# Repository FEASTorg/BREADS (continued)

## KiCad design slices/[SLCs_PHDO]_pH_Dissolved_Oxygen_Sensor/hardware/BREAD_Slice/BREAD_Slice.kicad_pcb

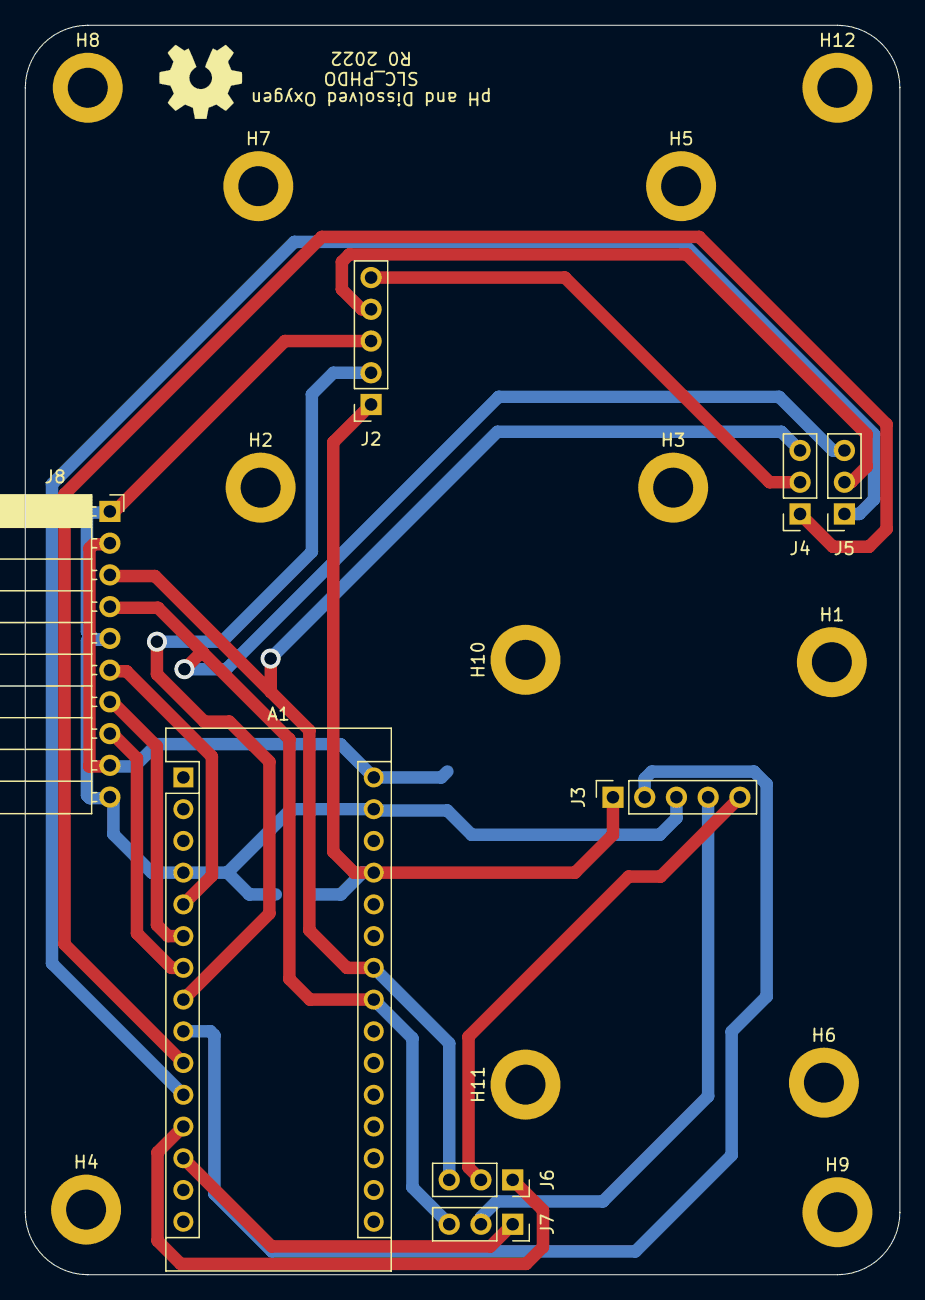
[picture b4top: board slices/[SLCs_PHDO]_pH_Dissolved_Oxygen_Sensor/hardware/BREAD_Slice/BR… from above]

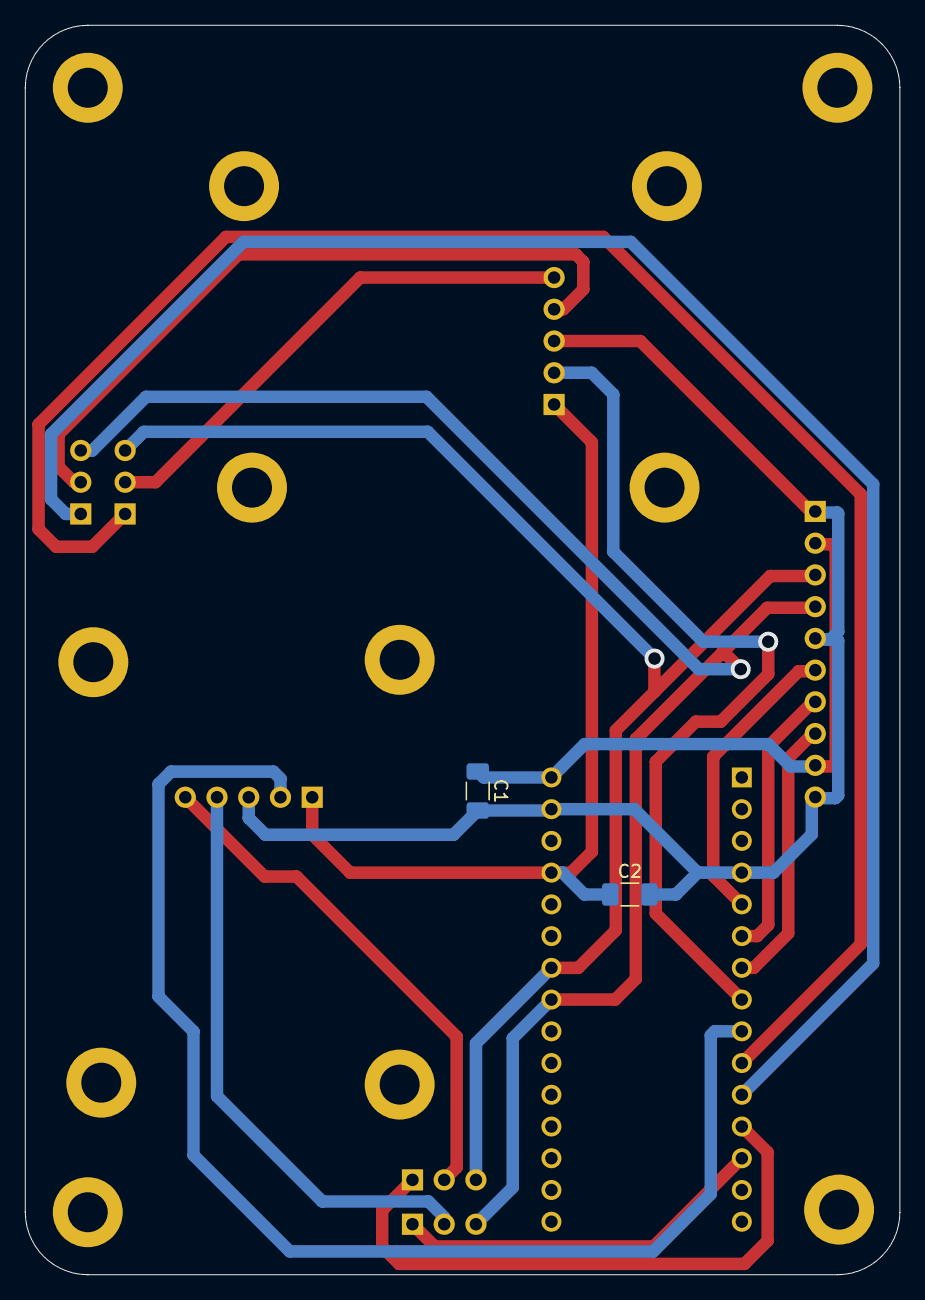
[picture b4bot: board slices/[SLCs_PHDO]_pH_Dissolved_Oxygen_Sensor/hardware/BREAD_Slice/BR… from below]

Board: 2 copper layers, 70.0 x 100.0 mm, 23 parts (2 on the bottom side), 15 nets.

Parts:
A1: Arduino_Nano_v3.x; Arduino_Nano
C1, C2: 10uF_t; C_1206_3216Metric_Pad1.33x1.80mm_HandSolder
H1, H2, H3, H4, H5, H6, H7, H8, H9, H10, H11, H12: MountingHole; MountingHole_3.2mm_M3_DIN965_Pad
J2, J3: Conn_01x05_Female; PinSocket_1x05_P2.54mm_Vertical
J4, J5, J6, J7: Conn_01x03_Male; PinSocket_1x03_P2.54mm_Vertical
J8: Conn_01x10_Female; PinSocket_1x10_P2.54mm_Horizontal
Logo1: Logo_Open_Hardware_Small; OSHW-Symbol_6.7x6mm_SilkScreen

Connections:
+5V: A1.27 (+5V), C2.1, J2.1, J3.1
+12V: A1.30 (VIN), C1.1, J8.2, J8.9
/I2C_CLK: A1.24 (A5), J4.3, J6.3
/I2C_DAT: A1.23 (A4), J5.3, J7.3
/OFFO2: A1.8 (D5), J2.2
/OFFpH: A1.9 (D6), J3.2
/RX1: A1.10 (D7), J4.1
/RX1/SCL: J2.5, J4.2
/RX2: A1.12 (D9), J6.1
/RX2/SCL: J3.5, J6.2
/TX1: A1.11 (D8), J5.1
/TX1/SDA: J2.4, J5.2
/TX2: A1.13 (D10), J7.1
/TX2/SDA: J3.4, J7.2
GND: A1.4 (GND), A1.29 (GND), C1.2, C2.2, J2.3, J3.3, J8.1, J8.5, J8.10
